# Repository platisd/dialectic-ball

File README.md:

# Dialectic Ball
Need to debug your code? Got stuck? Stack Overflow doesn't have the answer? Then ask Dialectic Ball!

## What?
The Dialectic Ball is a physical, [Magic 8-ball](https://en.wikipedia.org/wiki/Magic_8-Ball) inspired, debugging tool for your daily code struggles! Once you are out of ideas, pick up the Dialectic Ball and explain the problem you are facing with all its details. Remember, the Dialectic Ball is a delicate and highly advanced piece of technology, thus the more information you provide it and the more you outline the problem with all its aspects, the better the chance it will be able to assist you.

Once you are done illustrating your coding issue to it, shake Dialectic Ball until the progress bar is filled and wait for the answer! If you do not get a satisfactory answer then try again. Clarify the problem better, think of any crucial details that you might have omitted during the previous run and shake again. Keep on it, until you get a witty response that helps you solve the problem!

The Dialectic Ball is more like a [rubber duck](https://en.wikipedia.org/wiki/Rubber_duck_debugging) than a [Magic 8-ball](https://en.wikipedia.org/wiki/Magic_8-Ball), so **do not ask it yes-no questions**. That wouldn't be so dialectic, would it? Of course, you can always easily modify the code and make it answer whatever you wish.

### Usage manual
1. Pick up the Dialectic Ball and face the screen
2. Admire the 8-ball intro logo
3. Dialectic Ball will prompt you to ask your question
4. Take your time and ask your question, providing all the necessary details
5. When you are done, shake the ball until the progress bar on the bottom is filled up
6. The solution to your problems is presented to you
7. If you are satisfied with the response, put the Dialectic Ball facing downwards
8. If the answer did not help, shake again when prompted

## Why?
Despite our [impressive rubber duck collection](https://i.imgur.com/bP3KeV4.jpg) at the office, sometimes they fall short on feedback and interaction. In such occasions we often utilize a colleague, but this is admittedly not the most productive use of our colleagues. Dialectic Ball intends to fill this gap, i.e. a rubber duck that is able to provide feedback. As a bonus, shaking it is fun!

## How?
Dialectic Ball is comprised of an ATtiny84, connected to a GY-61 module (based on the ADXL335 accelerometer) and an LCD screen like the ones used on the old NOKIA phones! Two AAA batteries are powering the gadget up and a [3D printed case](https://www.tinkercad.com/things/4zkr0X7OHBL) encompasses everything, giving it a hemispherical shape. The PCB that routes everything together was manufactured by [JLCPCB](https://jlcpcb.com/), who will make your prototype PCB's for just 2$ and were kind enough to sponsor the `rev. 0` boards.

From a software perspective the microcontroller mainly remains in deep sleep mode, periodically waking up to turn the accelerometer on and read its measurements. If necessary, the screen will also be powered up and the appropriate messages will be displayed to the user. Specifically, the system wakes up when the ball is not facing downwards. Furthermore, the particular LCD screen consumes minimal power, even when displaying graphics, which makes it ideal for low power applications. Overall, the average power consumption of the gadget is around 10μA, enabling it to remain operational for years on those two batteries. Last but not least, the display is controlled via the [Nokia LCD](https://github.com/platisd/nokia-5110-lcd-library) library.

### Components
* [Dialectic Ball PCB](https://github.com/platisd/dialectic-ball/tree/master/hardware/eagle)
* ATTiny84-20PU
* DIP-14 socket
* AAA battery holders (2)
* Nokia LCD screen (**Important**: Get ones that have [this](https://i.imgur.com/MhUsdiz.jpg) pin layout)
* GY-61 accelerometer module
* Tactile button
* 10KΩ resistor
* 330Ω resistor
* [3D printed case](https://www.tinkercad.com/things/4zkr0X7OHBL-magic8ball)

## Media
* [Article on platis.solutions](https://platis.solutions/blog/2018/06/02/debug-your-code-with-dialectic-ball/)
* [Demo video](https://youtu.be/oXdIgaYoSw0)

## Similar projects
* [Programmer's Magic 8-ball](https://github.com/FareedQ/Programmer-s-Magic-8-Ball)

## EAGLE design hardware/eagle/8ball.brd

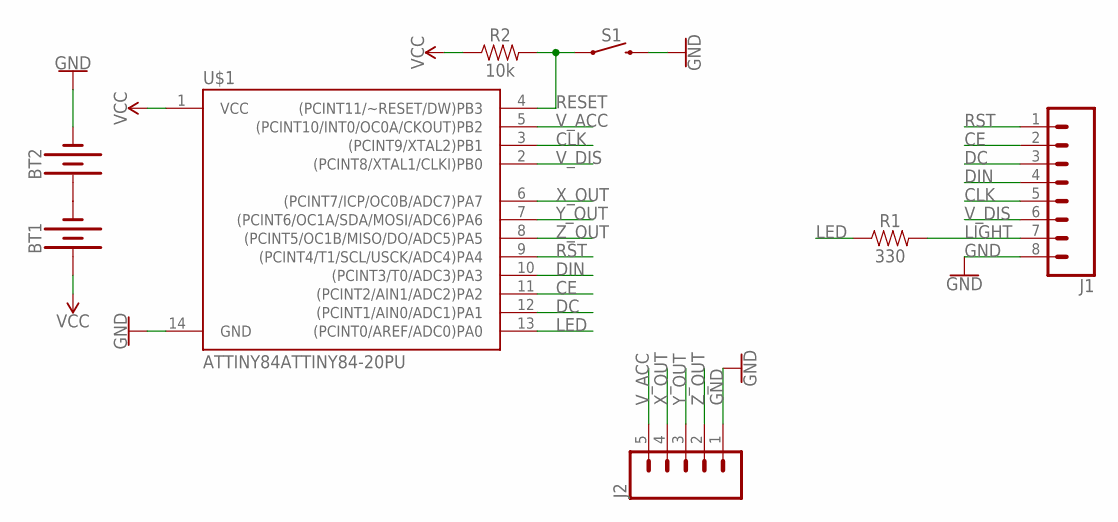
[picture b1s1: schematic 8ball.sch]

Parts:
BT1, BT2: BATTERY-AAA
J1: CONN_08FEMALE_LOCK; 1X08_FEMALE_LOCK
J2: CONN_05LOCK; 1X05_LOCK
R1: 330; AXIAL-0.3
R2: 10k; AXIAL-0.3
S1: MOMENTARY-SWITCH-SPST-PTH-6.0MM-KIT; TACTILE_SWITCH_PTH_6.0MM_KIT
U$1: ATTINY84ATTINY84-20PU; DIP14

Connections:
CE: J1.2, U$1.11 ((PCINT2/AIN1/ADC2)PA2)
CLK: J1.5, U$1.3 ((PCINT9/XTAL2)PB1)
DC: J1.3, U$1.12 ((PCINT1/AIN0/ADC1)PA1)
DIN: J1.4, U$1.10 ((PCINT3/T0/ADC3)PA3)
GND: BT2.GND@1 (-), J1.8, J2.1, S1.3 (2), U$1.14 (GND)
LED: R1.P$1 (1), U$1.13 ((PCINT0/AREF/ADC0)PA0)
LIGHT: J1.7, R1.P$2 (2)
unnamed: BT1.GND@1 (-), BT2.PWR@1 (+)
RESET: R2.P$2 (2), S1.1, U$1.4 ((PCINT11/~RESET/DW)PB3)
RST: J1.1, U$1.9 ((PCINT4/T1/SCL/USCK/ADC4)PA4)
VCC: BT1.PWR@1 (+), R2.P$1 (1), U$1.1 (VCC)
V_ACC: J2.5, U$1.5 ((PCINT10/INT0/OC0A/CKOUT)PB2)
V_DIS: J1.6, U$1.2 ((PCINT8/XTAL1/CLKI)PB0)
X_OUT: J2.4, U$1.6 ((PCINT7/ICP/OC0B/ADC7)PA7)
Y_OUT: J2.3, U$1.7 ((PCINT6/OC1A/SDA/MOSI/ADC6)PA6)
Z_OUT: J2.2, U$1.8 ((PCINT5/OC1B/MISO/DO/ADC5)PA5)

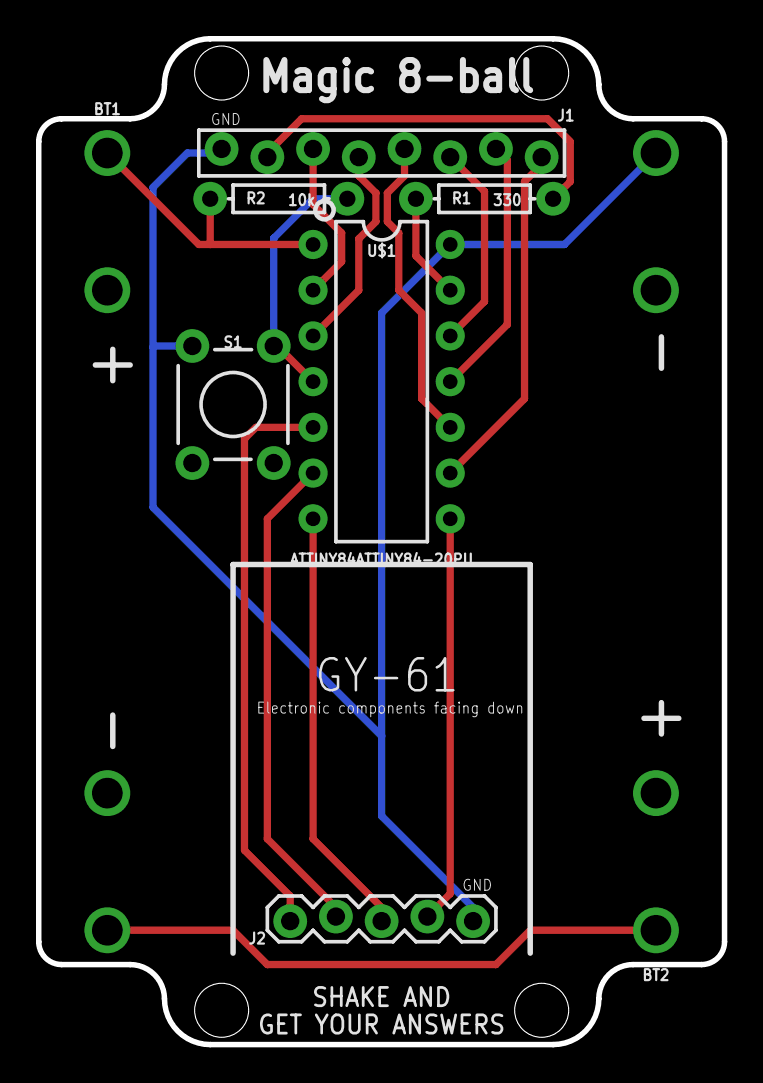
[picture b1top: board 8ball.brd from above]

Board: 2 copper layers, 38.1 x 55.9 mm, 8 parts (0 on the bottom side), 16 nets.

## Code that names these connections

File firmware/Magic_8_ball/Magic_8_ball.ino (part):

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  PLAYING,
};

const uint8_t V_ACC_PIN = 8; // PB2
const uint8_t CLK_PIN = 9; // PB1
const uint8_t V_DIS_PIN = 10; // PB0
const uint8_t X_OUT_PIN = A7; // PA7
const uint8_t Y_OUT_PIN = A6; // PA6
const uint8_t Z_OUT_PIN = A5; // PA5
const uint8_t RST_PIN = 4; // PA4
const uint8_t DIN_PIN = 3; // PA3
const uint8_t CE_PIN = 2; // PA2
const uint8_t DC_PIN = 1; // PA1
const uint8_t LED_PIN = 0; // PA0

// Input & output pins directly controlled in this scope
const uint8_t OUTPUT_PINS[] = {V_ACC_PIN, V_DIS_PIN, LED_PIN};
const uint8_t INPUT_PINS[] = {X_OUT_PIN, Y_OUT_PIN, Z_OUT_PIN};
const uint8_t LCD_DATA_PINS[] = {CLK_PIN, DIN_PIN, DC_PIN, CE_PIN, RST_PIN};

// The experimentally determined Z-axis value over which we consider
// ourselves to be facing up
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
volatile bool watchdogBarked = false;

Nokia_LCD lcd(CLK_PIN /* CLK */, DIN_PIN /* DIN */, DC_PIN /* DC */, CE_PIN /* CE */, RST_PIN /* RST */);
RunningState currentState = DEEP_SLEEP;
unsigned int amountOfMovements = 0;
int previousAcceleration = 0;
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
/*** Helper functions ***/
void turnScreenOn() {
  digitalWrite(V_DIS_PIN, HIGH);
}

void turnScreenOff() {
  digitalWrite(V_DIS_PIN, LOW);
  for (auto pin : LCD_DATA_PINS) {
    digitalWrite(pin, LOW);
  }
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void turnAccelerometerOn() {
  // Accelerometer needs some few milliseconds to get ready
  // so we need to make sure that we give it this time
  digitalWrite(V_ACC_PIN, HIGH);
  stayInDeepSleepFor(ACCELEROMETER_BOOTUP_TIME, WDT_16ms); // Give the accelerometer some time to boot
  enableADC();
}

void turnAccelerometerOff() {
  disableADC();
  digitalWrite(V_ACC_PIN, LOW);
}

unsigned int getAccelerationX() {
  return analogRead(X_OUT_PIN);
}

unsigned int getAccelerationY() {
  return analogRead(Y_OUT_PIN);
}

unsigned int getAccelerationZ() {
  return analogRead(Z_OUT_PIN);
}

unsigned int getAccelerationXYZ() {
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
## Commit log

2018-05-02 Add rev.0 hardware
2018-05-02 Add initial firmware
2018-05-03 Add initial 8ball game implementation
    TO-DO:
    * In check if the ball is facing up and increase
    the window length.
    * Draw better screens
    * Add useful tips that are to be randomized
2018-05-04 Add random suggestions/tips
    TO-DO:
    * Draw better screens (bitmaps)
2018-05-07 Add 8ball logo as intro
2018-05-21 Turn question and progress bars into bitmaps
2018-05-27 Fix current leak during deep sleep
    Unusually high power consumption (10-20ma) was observed when the system
    was put in DEEP_SLEEP mode after having previously been operational.
    The cause was that the pins controlling the data on the LCD screen were
    left in an undefined state after turning the screen on. As the Nokia_LCD
    class neither handles the screen when completely powered off nor cares for
    the state of the pins, its user has to set the state of those pins themselves.
2018-05-27 Small pedantic fixes
2018-05-28 Tweak parameters for better usability
    The ball now will respond faster to shaking
2018-05-28 Add awkward faces under the insightful tip :neckbeard:
    Awkward faces will now be shown randomly after every
    tip given by the magic ball.
2018-05-28 Add possibly the most useful tip
2018-05-28 Add initial README
2018-05-29 Decrease the overall reaction times to make the ball snappier
2018-05-29 Add usage instructions and hardware components
2018-05-29 Add links to demo video and article
2018-05-30 Add information on the display driver library
2018-05-30 Add link to 3d printed case
2018-05-30 Add dialectic ball image
2018-05-30 Add license
2018-06-02 Update readme
    * Fix link to article on platis.solutions
    * Add link for image of rubber duck collection
2018-06-16 Decrease watchdog timeout to match the sleep time accurately
2018-06-16 Rename header file types to cpp equivalents
2018-11-12 Avoid clearing the screen when not necessary
    When drawing the 8ball logo, it is not necessary to clear the screen before that
    since whatever leftovers exist will be overwritten by the drawing.

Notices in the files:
parts and their libraries:
SparkFun-Batteries: Licensing: Creative Commons ShareAlike 4.0 International - https://creativecommons.org/licenses/by-sa/4.0
